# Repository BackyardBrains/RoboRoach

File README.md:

RoboRoach
=========

The RoboRoach is the world's first commercially available cyborg! Created by Backyard Brains.  This repository contains the software, hardware, and firmware for the complete cyborg system. The hardware currently relies on the CC2540 and Blue Tooth Low Energy, so Apple MFI contracts to not apply.  To program, you will need a CC Debugger by TI <http://www.ti.com/tool/cc-debugger>.  The PCB is currently configured to use a TAG Connect port <http://www.tag-connect.com/catalog>. 

Overview
--------
Have you ever wanted to walk down the hall of your school or department with your own remote controlled cockroach? We are now excited to announce the world's first commercially available cyborg! With our RoboRoach you can briefly wirelessly control the left/right movement of a cockroach by microstimulation of the antenna nerves. The RoboRoach is a great way to learn about neurotechnology, learning, and electronics!

Hardware
--------
The PCB version 1.1 of the PCB Backpack contains 2 high-current digital outs for the two antennea.  We placed the backpack in it's own directory in case we decide to make a PCB for a bluetooth remote control that does not require a mobile device.

Firmware
--------
We tried 2 versions.  The first was using the BlueRadio AT.e firmware.  This allowed for UART debugging, but unforunately the API was too buggy.  We ended up swiching back to the TI BLE Stack, which allowed for lower level control of the timers and interrupts.  

Software
--------
Our release supports iOS and Android devices.  Native support is only for Apple mobile devices released after October 2011 (iPhone 4s and later) and Android devices running Android 4.3 or later (October 2013). 

We do not support Windows Phone at the moment. We also need to add support for native iPad interface, and add an OSX app interface too (the BLE code compiles on MacOSX, but we have no interface).

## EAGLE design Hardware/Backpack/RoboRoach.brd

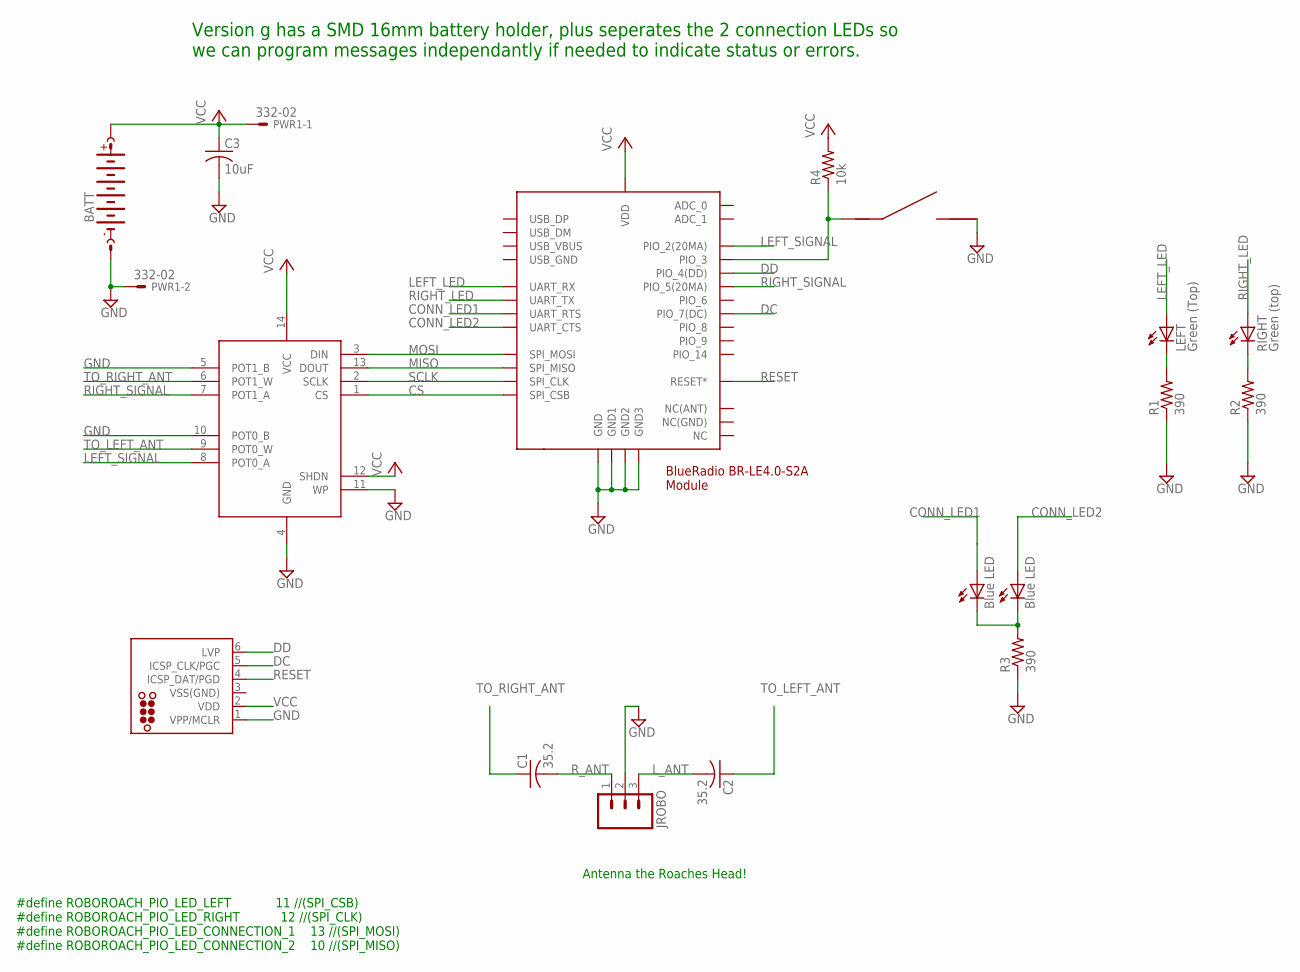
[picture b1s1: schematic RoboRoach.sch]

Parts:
BATT: BATTERY-16MMSMD; 16M_BATT_SMD
C1, C2: 35.2; C0805
C3: 10uF; C0805
CONNECTION, CONNECTION1: Blue LED; CHIPLED_1206
IC1: BR-LE4.0-S2; BR-LE4.0-X2A
J1: TC2030-MCP-NL
JROBO: M03PTH; 1X03
LEFT: Green (Top); CHIPLED_1206
POT: MCP4251; TSSOP14
PWR1: 332-02
R1, R2, R3: 390; R0805
R4: 10k; R0805
RIGHT: Green (top); CHIPLED_1206
U$2: B3U-1000X; B3U

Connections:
CONN_LED1: CONNECTION1.A, IC1.P$12 (UART_RTS)
CONN_LED2: CONNECTION.A, IC1.P$11 (UART_CTS)
CS: IC1.P$6 (SPI_CSB), POT.1 (CS)
DC: IC1.P$29 (PIO_7(DC)), J1.5 (ICSP_CLK/PGC)
DD: IC1.P$28 (PIO_4(DD)), J1.6 (LVP)
GND: BATT.NEG (-), C3.2, IC1.P$1 (GND), IC1.P$10 (GND1), IC1.P$20 (GND2), IC1.P$30 (GND3), J1.1 (VPP/MCLR), JROBO.2, POT.4 (GND), POT.5 (POT1_B), POT.10 (POT0_B), POT.11 (WP), PWR1.2, R1.1, R2.1, R3.1, U$2.PAD2
LEFT_LED: IC1.P$14 (UART_RX), LEFT.A
LEFT_SIGNAL: IC1.P$23 (PIO_2(20MA)), POT.8 (POT0_A)
L_ANT: C2.2, JROBO.3
MISO: IC1.P$5 (SPI_MISO), POT.13 (DOUT)
MOSI: IC1.P$8 (SPI_MOSI), POT.3 (DIN)
unnamed: LEFT.C, R1.2
unnamed: CONNECTION.C, CONNECTION1.C, R3.2
unnamed: IC1.P$26 (PIO_3), R4.1, U$2.PAD1
unnamed: R2.2, RIGHT.C
RESET: IC1.P$3 (RESET*), J1.4 (ICSP_DAT/PGD)
RIGHT_LED: IC1.P$13 (UART_TX), RIGHT.A
RIGHT_SIGNAL: IC1.P$24 (PIO_5(20MA)), POT.7 (POT1_A)
R_ANT: C1.2, JROBO.1
SCLK: IC1.P$7 (SPI_CLK), POT.2 (SCLK)
TO_LEFT_ANT: C2.1, POT.9 (POT0_W)
TO_RIGHT_ANT: C1.1, POT.6 (POT1_W)
VCC: BATT.POS1 (+), BATT.POS2 (+), C3.1, IC1.P$9 (VDD), J1.2 (VDD), POT.12 (SHDN), POT.14 (VCC), PWR1.1, R4.2
VSS(GND): J1.3 (VSS(GND))

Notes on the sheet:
Antenna the Roaches Head!
BlueRadio BR-LE4.0-S2A Module
#define ROBOROACH_PIO_LED_LEFT 11 //(SPI_CSB) #define ROBOROACH_PIO_LED_RIGHT 12 //(SPI_CLK) #define ROBOROACH_PIO_LED_CONNECTION_1 13 //(SPI_MOSI) #define ROBOROACH_PIO_LED_CONNECTION_2 10 //(SPI_MISO)
Version g has a SMD 16mm battery holder, plus seperates the 2 connection LEDs so we can program messages independantly if needed to indicate status or errors.

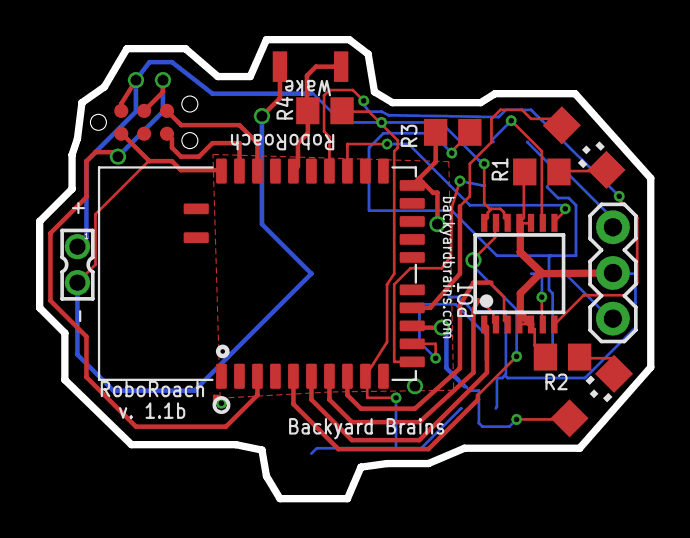
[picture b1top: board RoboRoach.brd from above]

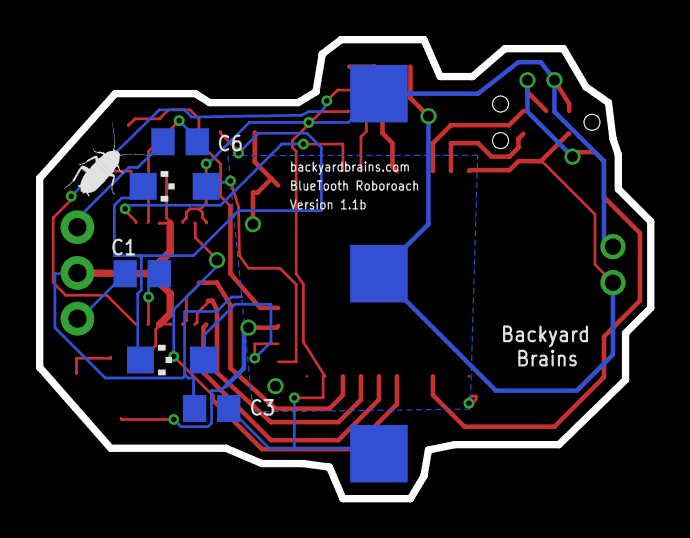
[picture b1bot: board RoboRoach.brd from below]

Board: 2 copper layers, 34.0 x 25.5 mm, 19 parts (7 on the bottom side), 23 nets.

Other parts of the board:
LOGOBOTTOM: BYBLOGO-S

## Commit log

2013-05-24 Initial Release
    Kinda works. Still needs iPad Interface, plus updated graphics, and UI
    layout cleanup,
2013-05-24 TI Firmware 0.2
    Based on the TI BLE-CC254x-1.3.1 Stack
2013-05-24 BlueRadio AT.e Firmware
    AT.e 1.2.1.3.1.1-BETA. Aborted due to bugs (Antenna stimulation
    failure, battery level not reporting properly, plus more) and slow
    updates.
2013-05-24 Updated readme.
2013-05-24 Added links to Readme
2013-05-24 More Updates to Readme
2013-05-24 Added picture
2013-11-02 Removed Static Frameworks from Source
2013-11-02 Readded Updated Frameworks
    Not sure if you are supposed to add these to GitHub... but adding just
    to be safe
2013-11-02 Fixed:
    *iOS7 Bug... Unable to write or read correctly
    *Numbers sometimes read as negative numbers on the Device
    *Gain setting now reads/writes correctly
    *Gain setting shows up in stimulation UI
    *UI Layout in 4" vs 3.5"
    *UI Layout in ios7 vs ios6
2013-11-02 Version 0.9:
    Updated for Firmware 0.3:
    + Duration is sent in 5ms Intervals, not Number of pulses.
    + Gain is sent in percentage from 0-100%, not 0-255.
    + Duration UI updated to show 5ms Intervals
    + Gain UI set to move in 5% intervals.
2013-11-03 Updated Icon. Bumped to version 1.0 Removed old SCTableView
2013-12-05 buildConfig.cfg
2013-12-21 Release 1.0
    Added Battery Check to read power level and display on Battery. Fixed
    crash when scrolling and returning from Segue.
2013-12-21 Cleaning up code that should not be on GitHub
    Removed Static Frameworks: TestFlight App and SensibleTableView
2013-12-21 Android RoboRoach App Initial Release
    Provides RoboRoach functionality for Android 4.3 phones and later
    (API18+)
2014-01-30 Adding PCB EagleCad Files and updating Readme
2014-08-22 Initial Release of RoboRoach 1.1b
    Final version of the initial RoboRoach release in Nov-2013
2014-08-22 Adding Support for CC2541
2016-03-27 Robo Roach project update
2016-03-27 Force update of firmware code files
2017-03-10 Bug where app crashed when it picked up near bluetooth devices without name is fixed
2017-03-10 Prepare Android release 1.1
2017-03-10 Next Android release is 1.2
2017-08-03 Update of RoboRoach to new xCode project
2017-08-03 Update RoboRoach project files
2017-08-03 Update BYB Github with code for connection to RoboRoach with greatest signal strength (closest one).
2017-08-03 Iconset added
2017-12-25 Gitignore added to Cypress
2017-12-25 First commit of Cypress RoboRoach BTLE project for PSoC Creator
2017-12-25 ADC for battery added on p3_0 (Ref 1.024V)
2017-12-28 Drawing of stimulation in debugged in iOS app
2017-12-28 Frequency error is lower by 10 folds
2017-12-28 Minimum frequency limited to 4 HZ
2017-12-29 iOS RoboRoach app updated to accept notifications from BT and config screen issues fixed
2018-01-03 PWM for LEDs changed to 25% and old POT_SHDN_1 pin deleted
2018-01-03 Battery levels animation for iOS app changed
2018-01-03 Comments added to code
2018-01-04 RTC Removed
2018-01-04 Code rearanged for lower power consumtion
2018-01-05 Low power mode implemented for BLESS subsystem on RR
2018-01-09 Comments added to new code for power optimization on RR
2018-02-06 * Gradle version updated to 3.0.1 * Compile SDK version updated to 27 * Build Tools version updated to 27.0.3
2018-02-07 * Fonts can now be applied directly in XML * Asking for location permission added (it's not possible to use BT without that anymore) * Gradle updated to version 4.1 * Build tools updated to version 2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
2018-02-07 Prepare Android release 1.2
2018-02-08 Problem with disconnecting is fixed now and selection of the nearest device (if there are more) is added
2021-02-17 Upgraded gradle and support switched to androidX
2021-02-17 Added missing ACCESS_FINE_LOCATION
2021-02-22 Build version 1.3

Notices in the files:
parts and their libraries:
tag-connect: ©2009 ROFA.cz - modified and updated by Robert Darlington ‹rdarlington@gmail.com›
